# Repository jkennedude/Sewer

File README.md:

# Sewer
A guitar effects pedal, based on the Proco-Rat, with custom mods for use with Bass and noise reduction

Version 2 makes some incremental improvements:
- SMD Layout for most of the board
- Mix knob converted to additive opamp clean blend for ease of use and to prevent volume drop when turning up clean mix
- Bass Switch simplified and made internal
- Better fit and finish

Specifications:
- Designed for a Hammond 125B enclosure with top mounted jacks
- Power: 9V DC center negative, no battery support
- Support for external bypass board enabling true or buffered bypass
- Input impedance: 1MOhms or more
- Output impedance: ~1KOhm
- Buffered clean blend
- Switchable distortion bass boost changes how much bass is distorted
- Swichable clipping diodes (by default either standard 1N914 or turbo-rat style red LEDs)

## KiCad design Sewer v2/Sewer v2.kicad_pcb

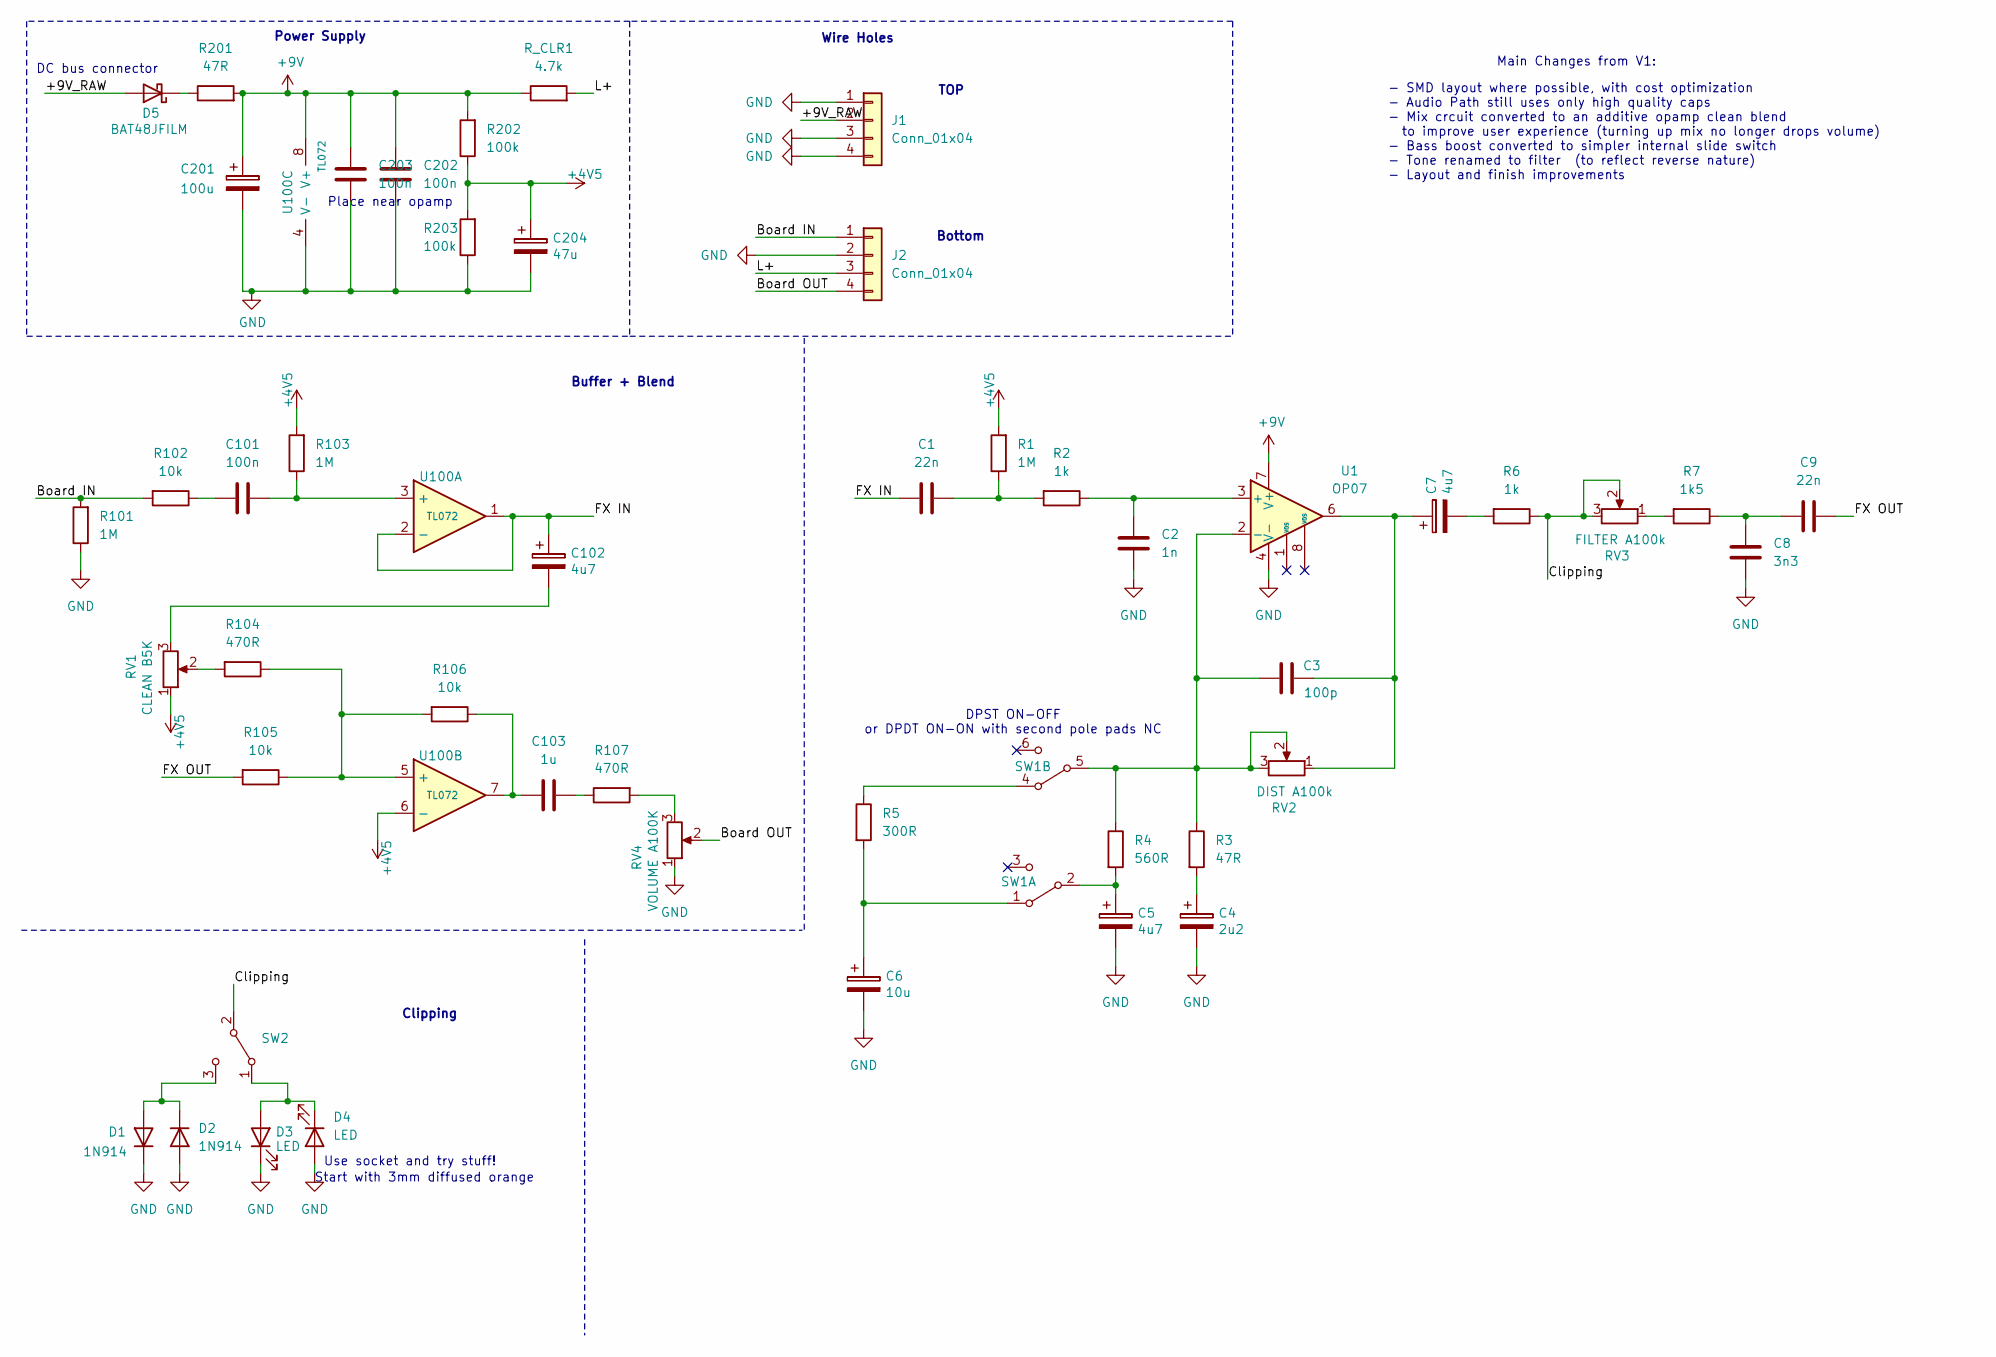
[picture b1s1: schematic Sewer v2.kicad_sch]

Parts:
C1, C9: 22n; TH_Film_Medium_2.5mm
C2: 1n; TH_Film_Medium_2.5mm
C3: 100p; SMD_Cap_0805; LCSC # C1790
C4: 2u2; SMD_Cap_D4; LCSC # C278511
C5, C7, C102: 4u7; SMD_Cap_D4; LCSC # C178620
C6: 10u; SMD_Cap_D4; LCSC # C178501
C8: 3n3; TH_Film_Medium_2.5mm
C101: 100n; TH_Film_Medium_2.5mm
C103: 1u; TH_Film_Thick_5mm
C201: 100u; TH_Cap_Lg_Radial_D7.5mm_P2.50mm
C202, C203: 100n; SMD_Cap_0805; LCSC # C28233
C204: 47u; TH_Cap_Med_Radial_D6.3mm_P2.50mm
D1, D2: 1N914; DO-35_P7.62mm
D3, D4: LED; LED_D3.0mm
D5: BAT48JFILM; D_SOD-323; LCSC # C2798199
J1, J2: Conn_01x04; SolderWire-0.25sqmm_1x04_P4.2mm_D0.65mm_OD1.7mm
R1, R101, R103: 1M; R_0805_2012Metric; LCSC # C17514
R2, R6: 1k; R_0805_2012Metric; LCSC # C17513
R3, R201: 47R; R_0805_2012Metric; LCSC # C17714
R4: 560R; R_0805_2012Metric; LCSC # C28636
R5: 300R; R_0805_2012Metric; LCSC # C17617
R7: 1k5; R_0805_2012Metric; LCSC # C4310
R102, R105, R106: 10k; R_0805_2012Metric; LCSC # C17414
R104, R107: 470R; R_0805_2012Metric; LCSC # C17710
R202, R203: 100k; R_1206_3216Metric; LCSC # C17900
RV1: CLEAN B5K; Pot_16mm
RV2: DIST A100k; Pot_16mm
RV3: FILTER A100k; Pot_16mm
RV4: VOLUME A100K; Pot_16mm
R_CLR1: 4.7k; R_1206_3216Metric; LCSC # C17936
SW1: DPDT_SLIDE_JLC_C108742; LCSC # C108742
SW2: Mini Switch SPDT
U1: OP07; SOIC-8_3.9x4.9mm_P1.27mm; LCSC # C7433
U100: TL072; SOIC-8_3.9x4.9mm_P1.27mm; LCSC # C6961

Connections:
+4V5: C204.1, R1.2, R103.2, R202.1, R203.2, RV1.1, U100.6 (-)
+9V: C201.1, C202.1, C203.1, R201.2, R202.2, R_CLR1.1, U1.7 (V+), U100.8 (V+)
/+9V_RAW: D5.2 (A), J1.2
/Board IN: J2.1, R101.2, R102.2
/Board OUT: J2.4, RV4.2
/Clipping: R6.1, RV3.2, RV3.3, SW2.2
/FX IN: C1.1, C102.1, U100.1, U100.2 (-)
/FX OUT: C9.1, R105.2
/L+: J2.3, R_CLR1.2
GND: C2.1, C4.2, C5.2, C6.2, C8.1, C201.2, C202.2, C203.2, C204.2, D1.1 (K), D2.2 (A), D3.1 (K), D4.2 (A), J1.1, J1.3, J1.4, J2.2, R101.1, R203.1, RV4.1, U1.4 (V-), U100.4 (V-)
unnamed: C1.2, R1.1, R2.2
unnamed: C3.1, C7.1, RV2.1, U1.6
unnamed: C4.1, R3.2
unnamed: C5.1, R4.2, SW1.2
unnamed: C6.1, R5.2, SW1.1
unnamed: C7.2, R6.2
unnamed: C8.2, C9.2, R7.1
unnamed: C101.1, R102.1
unnamed: C102.2, RV1.3
unnamed: C103.1, R107.1
unnamed: C103.2, R106.1, U100.7
unnamed: D1.2 (A), D2.1 (K), SW2.3
unnamed: D3.2 (A), D4.1 (K), SW2.1
unnamed: D5.1 (K), R201.1
unnamed: R5.1, SW1.4
unnamed: R7.2, RV3.1
unnamed: R104.2, RV1.2
unnamed: R107.2, RV4.3
unnamed: C2.2, R2.1, U1.3 (+)
unnamed: C3.2, R3.1, R4.1, RV2.2, RV2.3, SW1.5, U1.2 (-)
unnamed: C101.2, R103.1, U100.3 (+)
unnamed: R104.1, R105.1, R106.2, U100.5 (+)

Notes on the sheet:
Power Supply
- SMD layout where possible, with cost optimization - Audio Path still uses only high quality caps - Mix crcuit converted to an additive opamp clean blend to improve user experience (turning up mix no longer drops volume) - Bass boost converted to simpler internal slide switch - Tone renamed to fil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
Main Changes from V1:
Bottom
Buffer + Blend
Use socket and try stuff!
DPST ON-OFF or DPDT ON-ON with second pole pads NC
Start with 3mm diffused orange
DC bus connector
TOP
Wire Holes
Place near opamp
Clipping

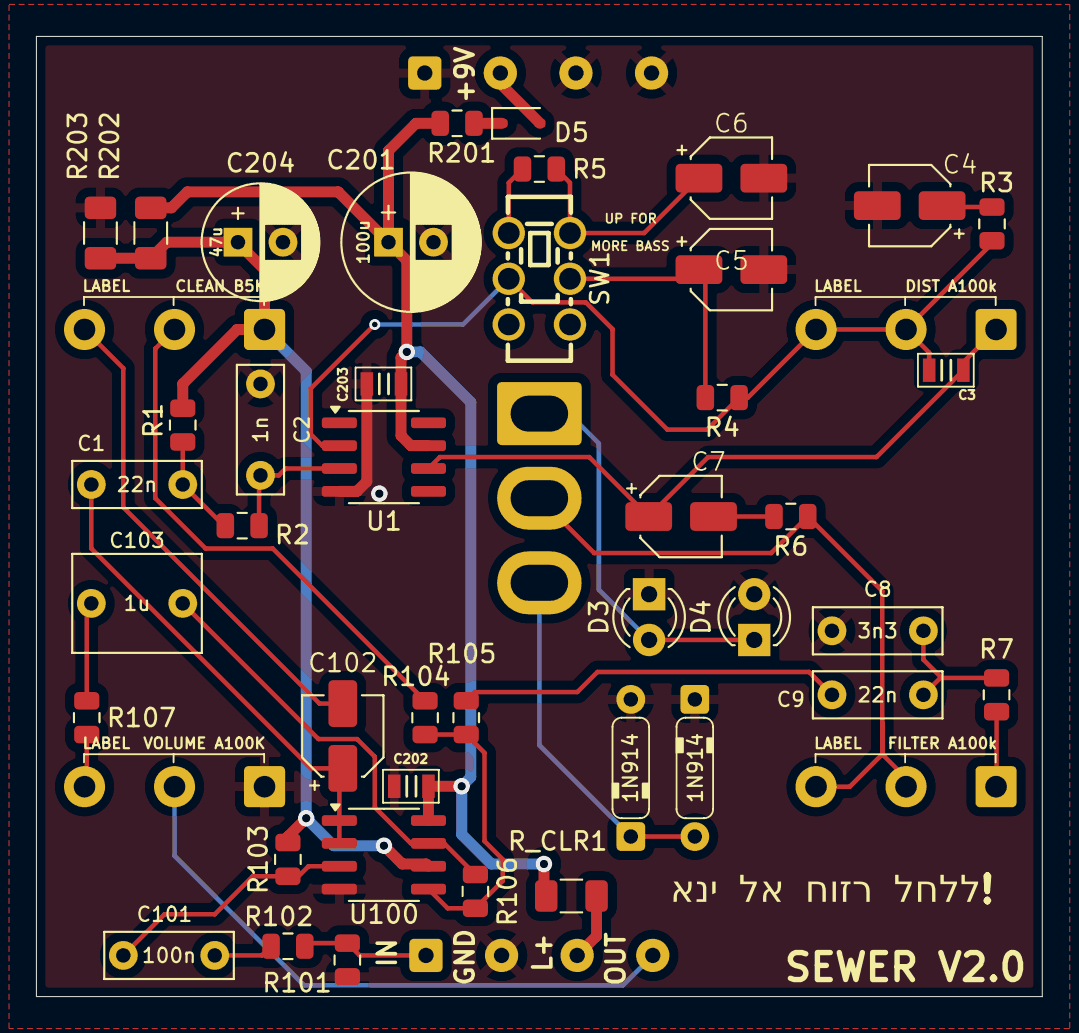
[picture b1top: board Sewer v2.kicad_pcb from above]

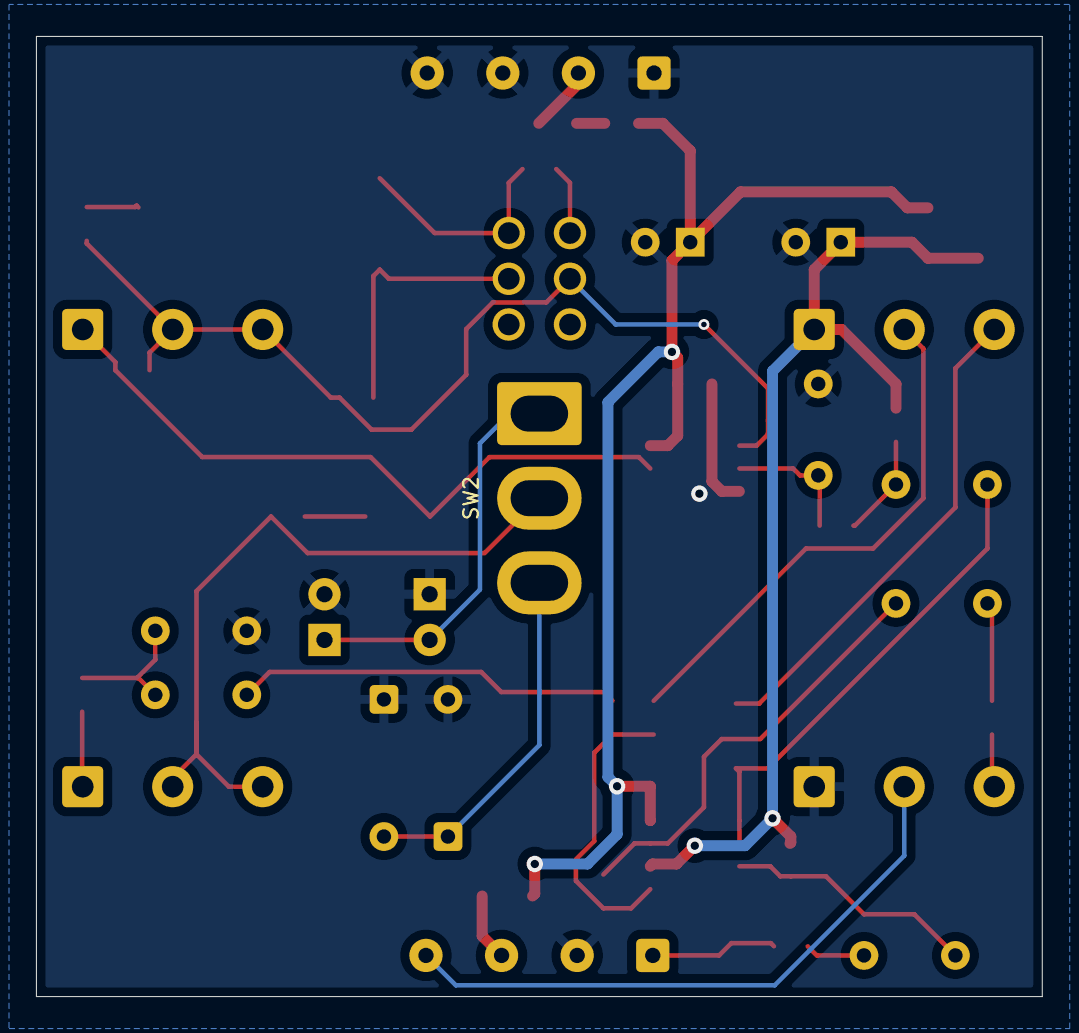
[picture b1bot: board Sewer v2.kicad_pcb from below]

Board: 2 copper layers, 55.9 x 53.3 mm, 49 parts (5 on the bottom side), 32 nets.

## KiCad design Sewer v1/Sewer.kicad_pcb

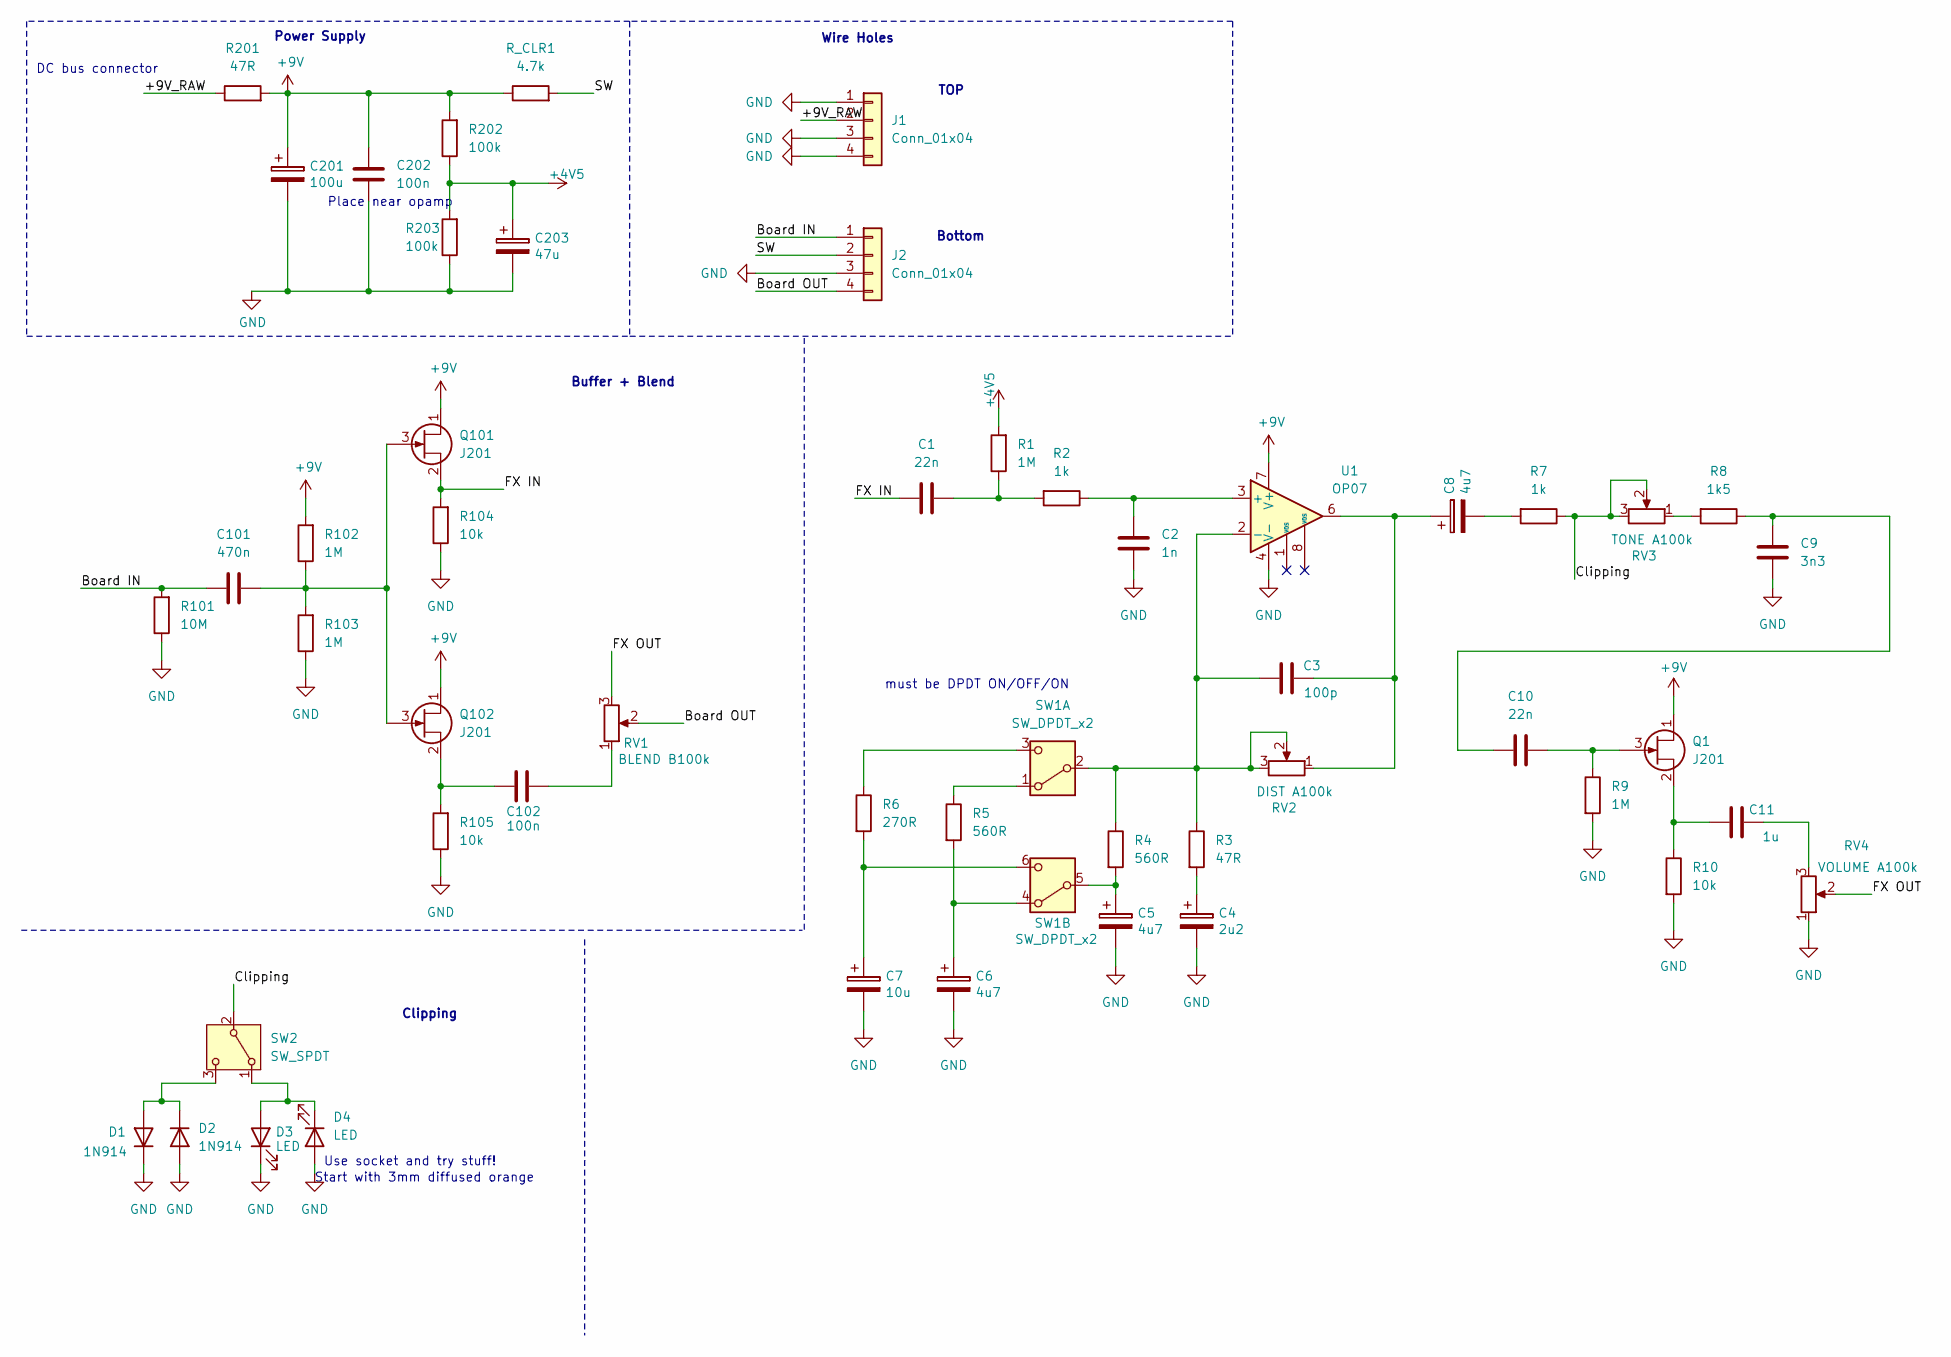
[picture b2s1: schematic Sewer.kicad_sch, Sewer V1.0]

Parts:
C1, C10: 22n; C_Rect_L7.2mm_W2.5mm_P5.00mm_FKS2_FKP2_MKS2_MKP2
C2: 1n; C_Rect_L7.2mm_W2.5mm_P5.00mm_FKS2_FKP2_MKS2_MKP2
C3: 100p; C_CERAMIC_DISC_D3.0mm_W1.6mm_P2.50mm
C4: 2u2; CP_Radial_D5.0mm_P2.00mm
C5, C6, C8: 4u7; CP_Radial_D5.0mm_P2.00mm
C7: 10u; CP_Radial_D5.0mm_P2.50mm
C9: 3n3; C_Rect_L7.2mm_W2.5mm_P5.00mm_FKS2_FKP2_MKS2_MKP2
C11: 1u; C_Rect_L7.2mm_W7.2mm_P5.00mm_FKS2_FKP2_MKS2_MKP2
C101: 470n; C_Rect_L7.2mm_W4.5mm_P5.00mm_FKS2_FKP2_MKS2_MKP2
C102, C202: 100n; C_Rect_L7.2mm_W2.5mm_P5.00mm_FKS2_FKP2_MKS2_MKP2
C201: 100u; CP_Radial_D5.0mm_P2.50mm
C203: 47u; CP_Radial_D5.0mm_P2.50mm
D1, D2: 1N914; D_DO-35_SOD27_P7.62mm_Horizontal
D3, D4: LED; LED_D3.0mm
J1, J2: Conn_01x04; SolderWire-0.25sqmm_1x04_P4.2mm_D0.65mm_OD1.7mm
Q1, Q101, Q102: J201; SOT-23_Handsoldering
R1, R9, R102, R103: 1M; RES_0.25watt_L3.6mm_D1.6mm_P7.62mm_Horizontal
R2, R7: 1k; RES_0.25watt_L3.6mm_D1.6mm_P7.62mm_Horizontal
R3, R201: 47R; RES_0.25watt_L3.6mm_D1.6mm_P7.62mm_Horizontal
R4, R5: 560R; RES_0.25watt_L3.6mm_D1.6mm_P7.62mm_Horizontal
R6: 270R; RES_0.25watt_L3.6mm_D1.6mm_P7.62mm_Horizontal
R8: 1k5; RES_0.25watt_L3.6mm_D1.6mm_P7.62mm_Horizontal
R10, R104, R105: 10k; RES_0.25watt_L3.6mm_D1.6mm_P7.62mm_Horizontal
R101: 10M; RES_0.25watt_L3.6mm_D1.6mm_P7.62mm_Horizontal
R202, R203: 100k; RES_0.25watt_L3.6mm_D1.6mm_P7.62mm_Horizontal
RV1: BLEND B100k; POT_16MM
RV2: DIST A100k; POT_16MM
RV3: TONE A100k; POT_16MM
RV4: VOLUME A100k; POT_16MM
R_CLR1: 4.7k; RES_0.25watt_L3.6mm_D1.6mm_P7.62mm_Horizontal
SW1: SW_DPDT_x2; DPDT.LUGS
SW2: SW_SPDT
U1: OP07; DIP-8_W7.62mm

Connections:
+4V5: C203.1, R1.2, R202.1, R203.2
+9V: C201.1, C202.1, Q1.1 (D), Q101.1 (D), Q102.1 (D), R102.2, R201.2, R202.2, R_CLR1.1, U1.7 (V+); also elsewhere on the board
/+9V_RAW: J1.2, R201.1
/Board IN: C101.1, J2.1, R101.2
/Board OUT: J2.4, RV1.2
/Clipping: R7.1, RV3.2, RV3.3, SW2.2 (B)
/FX IN: C1.1, Q101.2 (S), R104.2
/FX OUT: RV1.3, RV4.2
/SW: J2.2, R_CLR1.2; also elsewhere on the board
GND: C2.1, C4.2, C5.2, C6.2, C7.2, C9.1, C201.2, C202.2, C203.2, D1.1 (K), D2.2 (A), D3.1 (K), D4.2 (A), J1.1, J1.3, J1.4, J2.3, R9.2, R10.2, R101.1, R103.1, R104.1, R105.1, R203.1, RV4.1, U1.4 (V-)
unnamed: C1.2, R1.1, R2.2
unnamed: C3.1, C8.1, RV2.1, U1.6
unnamed: C4.1, R3.2
unnamed: C8.2, R7.2
unnamed: C9.2, C10.2, R8.1
unnamed: C11.1, RV4.3
unnamed: C102.2, RV1.1
unnamed: D1.2 (A), D2.1 (K), SW2.3 (C)
unnamed: D3.2 (A), D4.1 (K), SW2.1 (A)
unnamed: C10.1, Q1.3 (G), R9.1
unnamed: C11.2, Q1.2 (S), R10.1
unnamed: C101.2, Q101.3 (G), Q102.3 (G), R102.1, R103.2
unnamed: C102.1, Q102.2 (S), R105.2
unnamed: R8.2, RV3.1
unnamed: R5.1, SW1.1 (A)
unnamed: C3.2, R3.1, R4.1, RV2.2, RV2.3, SW1.2 (B), U1.2 (-)
unnamed: R6.1, SW1.3 (C)
unnamed: C6.1, R5.2, SW1.4 (A)
unnamed: C5.1, R4.2, SW1.5 (B)
unnamed: C7.1, R6.2, SW1.6 (C)
unnamed: C2.2, R2.1, U1.3 (+)

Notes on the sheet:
DC bus connector
Place near opamp
Use socket and try stuff!
Wire Holes
Buffer + Blend
Start with 3mm diffused orange
Bottom
Power Supply
Clipping
TOP
must be DPDT ON/OFF/ON

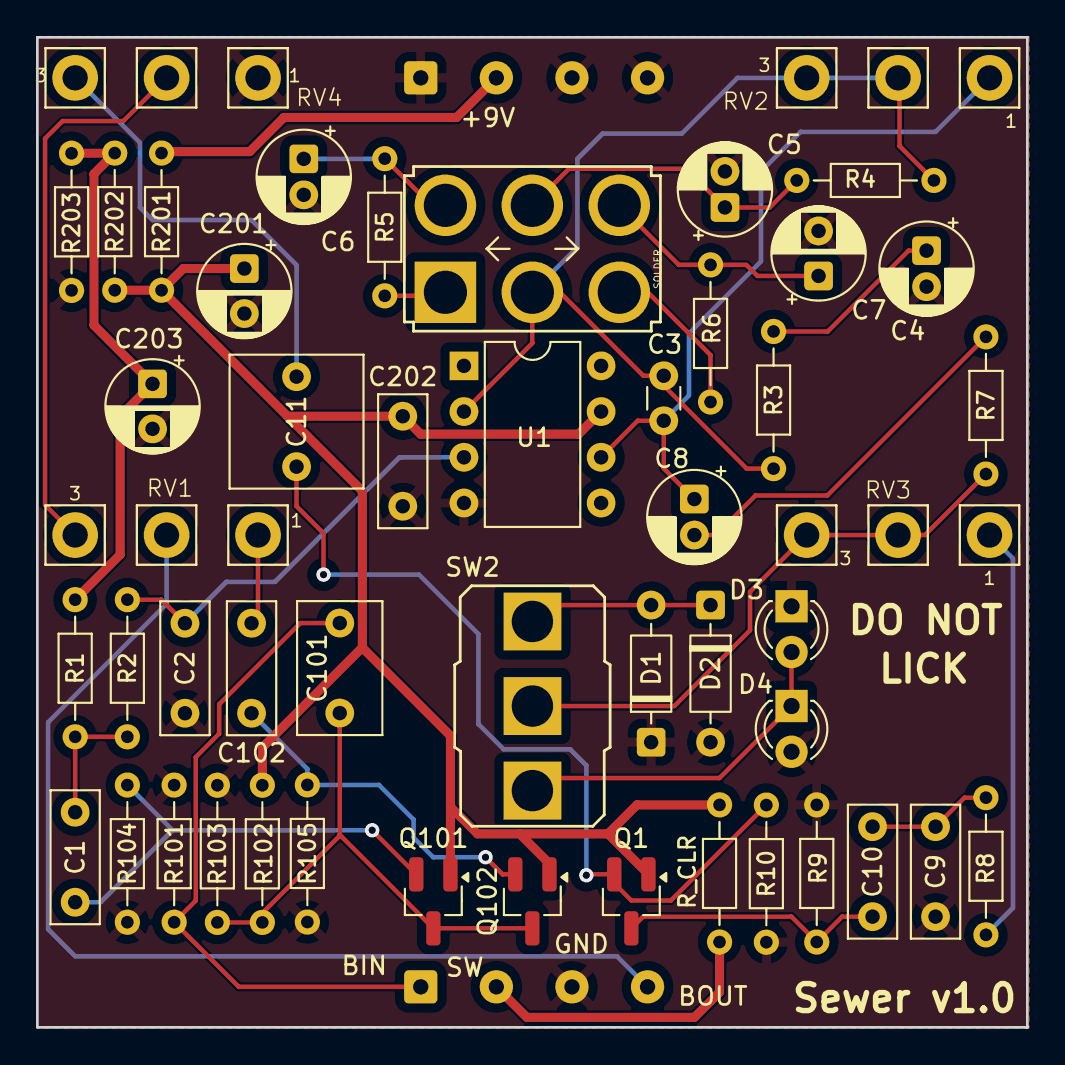
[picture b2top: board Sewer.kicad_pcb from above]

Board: 2 copper layers, 55.0 x 55.0 mm, 51 parts (0 on the bottom side), 31 nets.

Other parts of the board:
R_CLR: 4.7k; RES_0.25watt_L3.6mm_D1.6mm_P7.62mm_Horizontal

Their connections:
+9V: R_CLR.1; also elsewhere on the board
/SW: R_CLR.2; also elsewhere on the board

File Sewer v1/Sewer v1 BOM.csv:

Id,Designator,Footprint,Quantity,Designation,Supplier and ref,Column1,_1
1,R_CLR,RES_0.25watt_L3.6mm_D1.6mm_P7.62mm_Horizontal,1,4.7k,,,
2,"R103,R102,R9,R1",RES_0.25watt_L3.6mm_D1.6mm_P7.62mm_Horizontal,4,1M,,,
3,"D3,D4",LED_D3.0mm,2,LED,,,
4,"D2,D1",D_DO-35_SOD27_P7.62mm_Horizontal,2,1N914,,,
5,"R10,R104,R105",RES_0.25watt_L3.6mm_D1.6mm_P7.62mm_Horizontal,3,10k,,,
6,C9,C_Rect_L7.2mm_W2.5mm_P5.00mm_FKS2_FKP2_MKS2_MKP2,1,3n3,,,
7,"C10,C1",C_Rect_L7.2mm_W2.5mm_P5.00mm_FKS2_FKP2_MKS2_MKP2,2,22n,,,
8,R8,RES_0.25watt_L3.6mm_D1.6mm_P7.62mm_Horizontal,1,1k5,,,
9,"Q102,Q101,Q1",SOT-23_Handsoldering,3,J201,,,
10,C11,C_Rect_L7.2mm_W7.2mm_P5.00mm_FKS2_FKP2_MKS2_MKP2,1,1u,,,
11,"R2,R7",RES_0.25watt_L3.6mm_D1.6mm_P7.62mm_Horizontal,2,1k,,,
12,U1,DIP-8_W7.62mm,1,OP07,,,
13,RV2,POT_16MM,1,DIST A100k,,,
14,RV3,POT_16MM,1,TONE A100k,,,
15,RV4,POT_16MM,1,VOLUME A100k,,,
16,RV1,POT_16MM,1,BLEND B100k,,,
17,SW1,DPDT.LUGS,1,SW_DPDT_x2,,,
18,C203,CP_Radial_D5.0mm_P2.50mm,1,47u,,,
19,R6,RES_0.25watt_L3.6mm_D1.6mm_P7.62mm_Horizontal,1,270R,,,
20,"C102,C202",C_Rect_L7.2mm_W2.5mm_P5.00mm_FKS2_FKP2_MKS2_MKP2,2,100n,,,
21,C4,CP_Radial_D5.0mm_P2.00mm,1,2u2,,,
22,"J2,J1",SolderWire-0.25sqmm_1x04_P4.2mm_D0.65mm_OD1.7mm,2,Conn_01x04,,,
23,C3,C_CERAMIC_DISC_D3.0mm_W1.6mm_P2.50mm,1,100p,,,
24,"R3,R201",RES_0.25watt_L3.6mm_D1.6mm_P7.62mm_Horizontal,2,47R,,,
25,"R4,R5",RES_0.25watt_L3.6mm_D1.6mm_P7.62mm_Horizontal,2,560R,,,
26,R101,RES_0.25watt_L3.6mm_D1.6mm_P7.62mm_Horizontal,1,10M,,,
27,C7,CP_Radial_D5.0mm_P2.50mm,1,10u,,,
28,C2,C_Rect_L7.2mm_W2.5mm_P5.00mm_FKS2_FKP2_MKS2_MKP2,1,1n,,,
29,"C6,C8,C5",CP_Radial_D5.0mm_P2.00mm,3,4u7,,,
30,C101,C_Rect_L7.2mm_W4.5mm_P5.00mm_FKS2_FKP2_MKS2_MKP2,1,470n,,,
31,C201,CP_Radial_D5.0mm_P2.50mm,1,100u,,,
32,"R202,R203",RES_0.25watt_L3.6mm_D1.6mm_P7.62mm_Horizontal,2,100k,,,
33,SW2,SW_SPDT,1,SW_SPDT,,,

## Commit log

2026-03-09 Initial readme
2026-03-09 Add v1 files
2026-03-09 Add v2
